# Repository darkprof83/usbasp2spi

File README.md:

# usbasp2spi
A adapter board for programming BIOS chips using an upgraded usbasp programmer.

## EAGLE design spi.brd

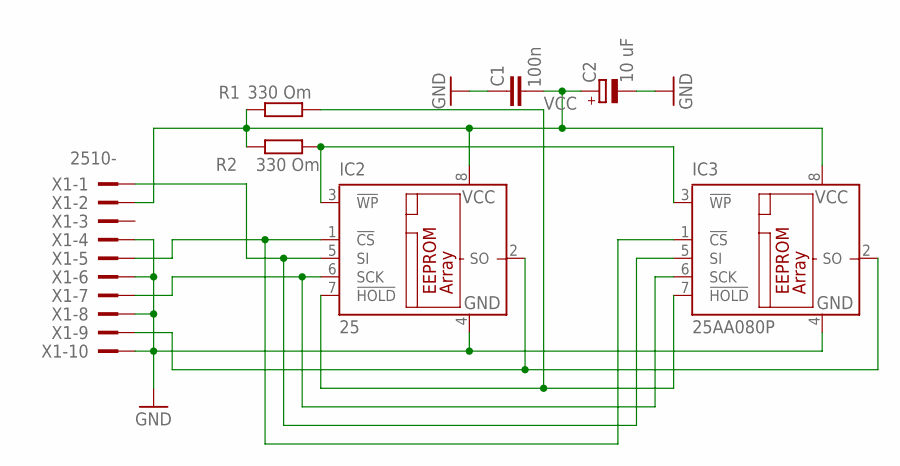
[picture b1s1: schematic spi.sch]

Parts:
C1: 100n; C0805K
C2: 10 uF; SMC_D
IC2: 25; SO-08M
IC3: 25AA080P; DIL8
R1, R2: 330 Om; 0204/7
X1: 2510-; PAK100/2500-10

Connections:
CS: IC2.1 (!CS), IC3.1 (!CS), X1.5
GND: C1.2, C2.-, IC2.4 (GND), IC3.4 (GND), X1.4, X1.6, X1.8, X1.10
HOLD: IC2.7 (!HOLD), IC3.7 (!HOLD), R2.1
SCK: IC2.6 (SCK), IC3.6 (SCK), X1.7
SI: IC2.5 (SI), IC3.5 (SI), X1.1
SO: IC2.2 (SO), IC3.2 (SO), X1.9
VCC: C1.1, C2.+, IC2.8 (VCC), IC3.8 (VCC), R1.1, R2.2, X1.2
WP: IC2.3 (!WP), IC3.3 (!WP), R1.2

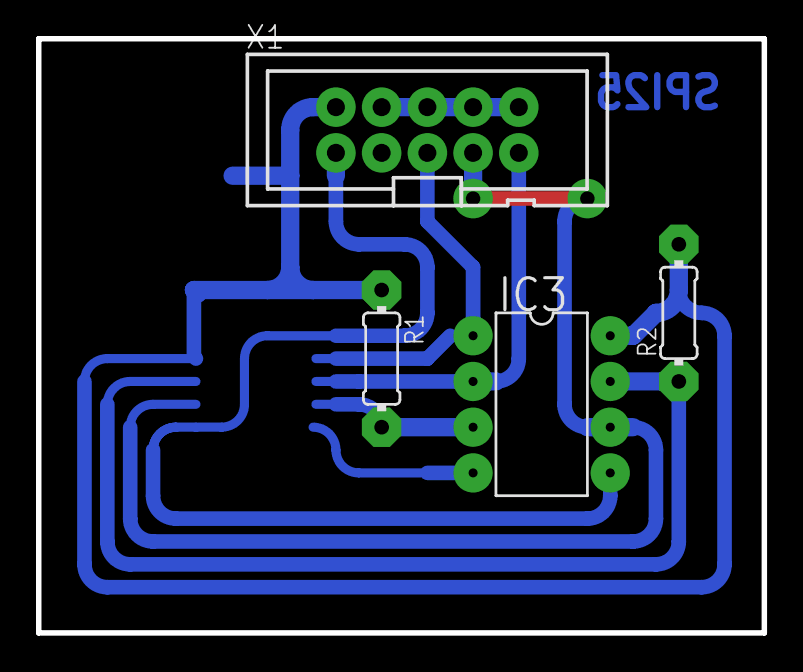
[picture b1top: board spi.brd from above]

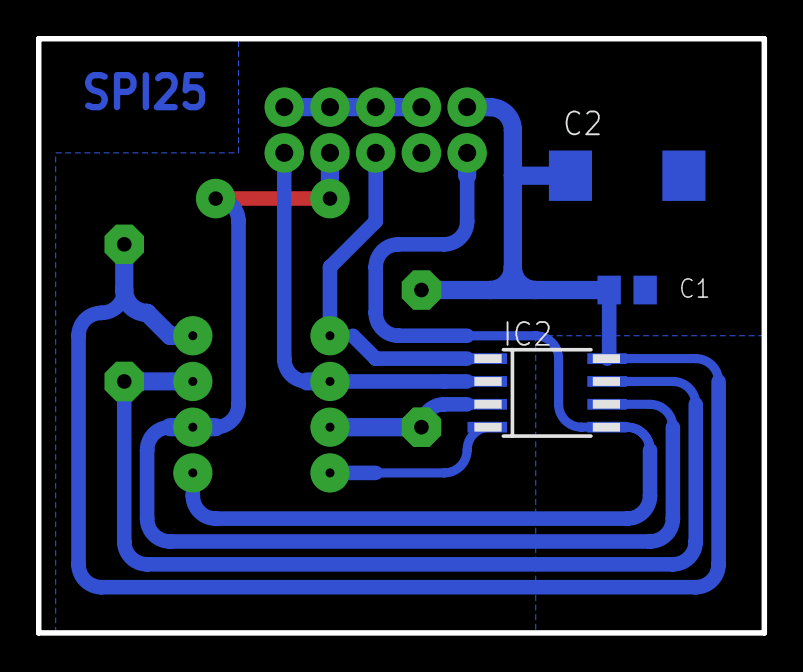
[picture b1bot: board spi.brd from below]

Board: 2 copper layers, 40.3 x 33.0 mm, 7 parts (3 on the bottom side), 8 nets.

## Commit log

2018-08-19 Черновой вариант платы spi переходника.
2018-08-19 Added license file
2018-08-19 Added ground polygon
2018-08-19 Added spi25 scheme
2018-08-19 Renamed net
2018-08-19 Fixed DRC bugs
2018-08-19 Fixed spi25 label
2018-08-19 Added lay files to ignore
2018-08-23 Fixed polygon
2020-05-05 Увеличено расстояние между дорожкой и площадкой
2020-05-05 Добавлены конденсаторы по питанию
2020-05-05 Исправлено посадочное место под планарную микросхему
2020-05-06 Исправлена заливка возле конденсатора на 100 nF
2020-05-07 Диаметр отверстий 0.3 мм, диаметр площадок 2.2 мм
2020-05-07 Изменены настройки cam процессора
2020-05-07 Изменен диаметр площадок разъема
2020-05-07 Изменен размер via площадок
2020-05-07 Изменены площадки микросхемы
2020-05-07 pdf файлы игнорируются
2020-05-07 25 серия использует so-8 в 200 mil
2020-05-07 Подправлена заливка возле минусовой шины
2020-05-07 Обновлен cam файл
2020-10-05 Увеличина ширина контура платы
